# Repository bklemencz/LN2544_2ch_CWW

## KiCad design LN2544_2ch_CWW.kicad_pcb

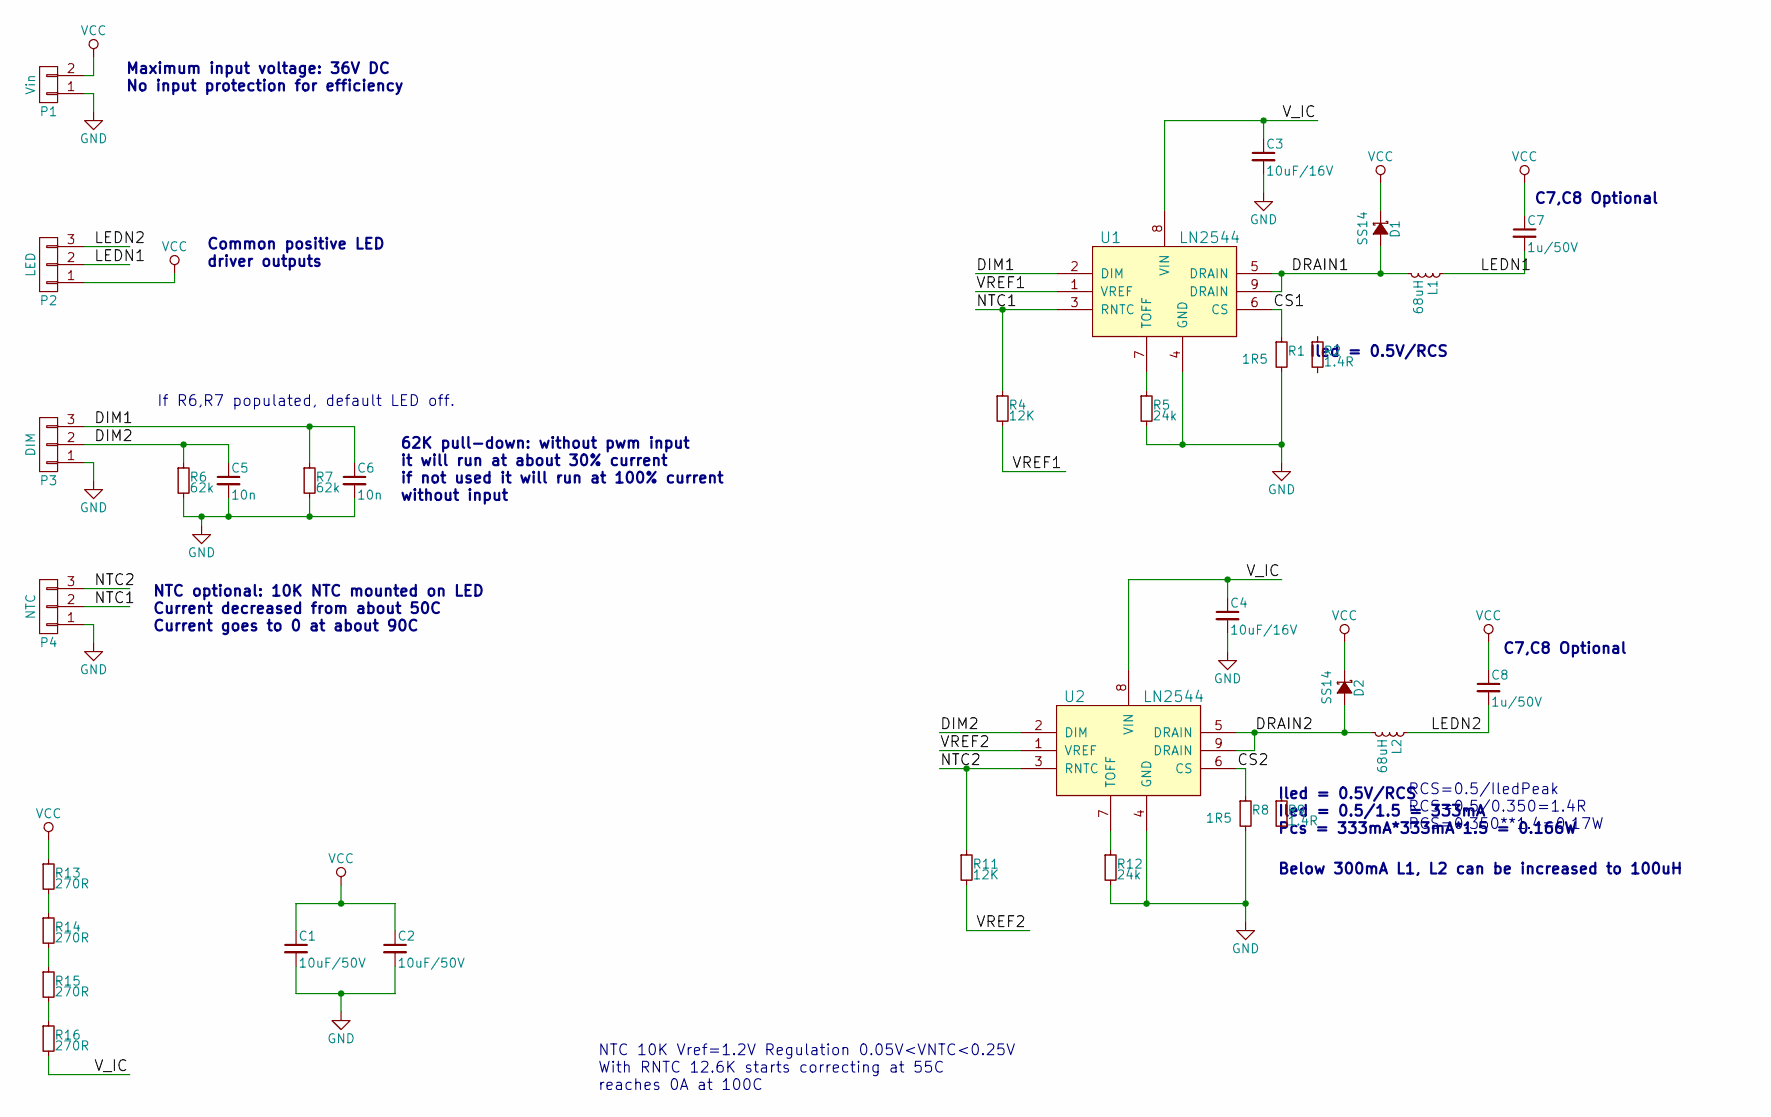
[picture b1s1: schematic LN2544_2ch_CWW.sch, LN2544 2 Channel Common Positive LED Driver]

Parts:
C1, C2: 10uF/50V; C_1206
C3, C4: 10uF/16V; C_0805
C5, C6: 10n; C_0805
C7, C8: 1u/50V; C_1206
D1, D2: SS14; D_SMA
L1, L2: 68uH; IND_SMD_CD54
P1: Vin; Pin_Header_Straight_1x02_Pitch2.54mm
P2: LED; Pin_Header_Straight_1x03_Pitch2.54mm
P3: DIM; Pin_Header_Straight_1x03_Pitch2.54mm
P4: NTC; Pin_Header_Straight_1x03_Pitch2.54mm
R1, R8: 1R5; R_1210
R2, R9: 1.4R; R_0805
R4, R11: 12K; R_0805
R5, R12: 24k; R_0805
R6, R7: 62k; R_0805
R13, R14, R15, R16: 270R; R_1206
U1, U2: LN2544; SOIC-8-1EP_3.9x4.9mm_Pitch1.27mm

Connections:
/CS1: R1.1, U1.6 (CS)
/CS2: R8.1, U2.6 (CS)
/DIM1: C6.1, P3.3, R7.1, U1.2 (DIM)
/DIM2: C5.1, P3.2, R6.1, U2.2 (DIM)
/DRAIN1: D1.2 (A), L1.2, U1.5 (DRAIN), U1.9 (DRAIN)
/DRAIN2: D2.2 (A), L2.2, U2.5 (DRAIN), U2.9 (DRAIN)
/LEDN1: C7.2, L1.1, P2.2
/LEDN2: C8.2, L2.1, P2.3
/NTC1: P4.2, R4.1, U1.3 (RNTC)
/NTC2: P4.3, R11.1, U2.3 (RNTC)
/VREF1: R4.2, U1.1 (VREF)
/VREF2: R11.2, U2.1 (VREF)
/V_IC: C3.1, C4.1, R16.2, U1.8 (VIN), U2.8 (VIN)
GND: C1.2, C2.2, C3.2, C4.2, C5.2, C6.2, P1.1, P3.1, P4.1, R1.2, R5.2, R6.2, R7.2, R8.2, R12.2, U1.4 (GND), U2.4 (GND)
unnamed: R5.1, U1.7 (TOFF)
unnamed: R12.1, U2.7 (TOFF)
unnamed: R13.2, R14.1
unnamed: R14.2, R15.1
unnamed: R15.2, R16.1
VCC: C1.1, C2.1, C7.1, C8.1, D1.1 (K), D2.1 (K), P1.2, P2.1, R13.1

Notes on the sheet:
Iled = 0.5V/RCS
Iled = 0.5V/RCS Iled = 0.5/1.5 = 333mA Pcs = 333mA*333mA*1.5 = 0.166W
C7,C8 Optional
62K pull-down: without pwm input it will run at about 30% current if not used it will run at 100% current without input
Common positive LED driver outputs
NTC optional: 10K NTC mounted on LED Current decreased from about 50C Current goes to 0 at about 90C
Maximum input voltage: 36V DC No input protection for efficiency
Below 300mA L1, L2 can be increased to 100uH
NTC 10K Vref=1.2V Regulation 0.05V<VNTC<0.25V With RNTC 12.6K starts correcting at 55C reaches 0A at 100C
RCS=0.5/IledPeak RCS=0.5/0.350=1.4R PCS=0.350**1.4=0.17W
If R6,R7 populated, default LED off.

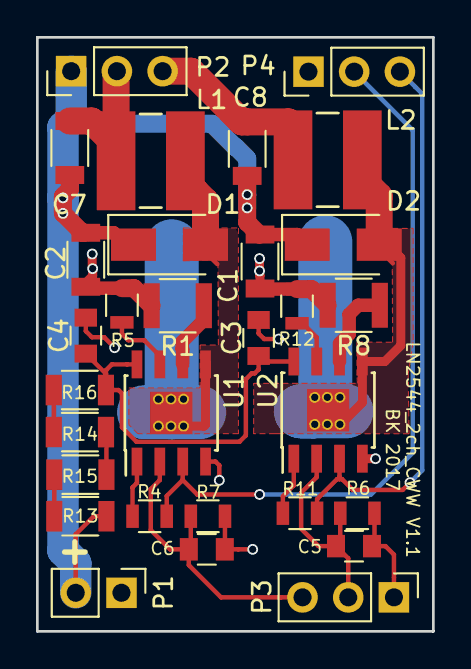
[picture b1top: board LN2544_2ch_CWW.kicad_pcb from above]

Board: 2 copper layers, 22.0 x 33.0 mm, 30 parts (0 on the bottom side), 20 nets.

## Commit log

2017-06-19 :lollipop: Added .gitattributes & .gitignore files
2017-06-19 initial
2017-06-21 PCB Update
2017-06-22 Gerber Out
2017-11-12 V1.1 Update
2017-11-12 Upd 1.1
2017-11-12 Clean
2017-11-12 V1.1 Gerber Update
